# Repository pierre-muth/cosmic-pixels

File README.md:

# cosmic-pixels
Code and files of the cosmic-pixels project on www.pierremuth.com

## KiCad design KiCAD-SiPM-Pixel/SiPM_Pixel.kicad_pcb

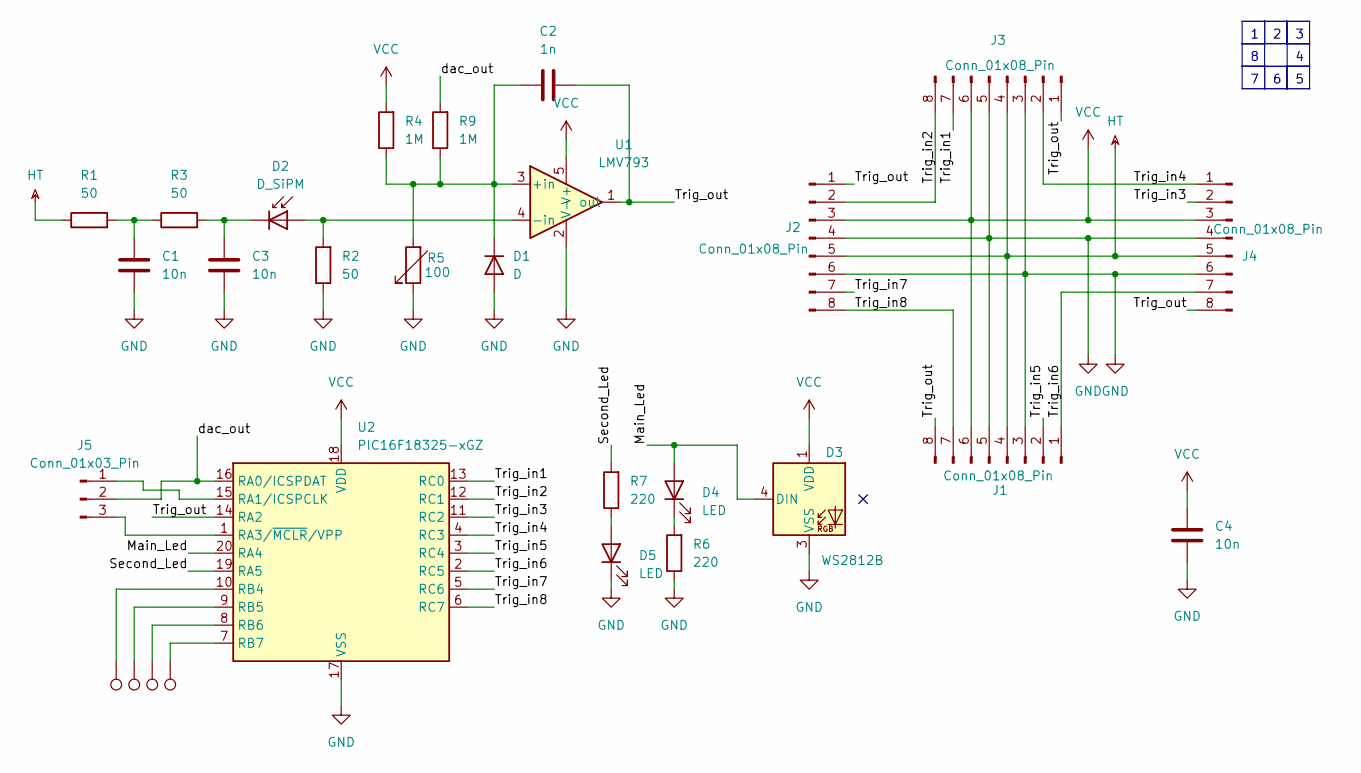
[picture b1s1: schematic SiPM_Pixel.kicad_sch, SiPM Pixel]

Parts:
C1, C3, C4: 10n; C_0805_2012Metric_Pad1.18x1.45mm_HandSolder
C2: 1n; C_0805_2012Metric_Pad1.18x1.45mm_HandSolder
D1: D; D_0805_2012_long_HandSolder
D2: D_SiPM; PinSocket_1x02_P2.54mm_Vertical
D3: WS2812B; LED_WS2812B_5.0x5.0mm_3Pin
D4, D5: LED; LED_0805_2012Metric_Pad1.15x1.40mm_HandSolder
J1, J2, J3, J4: Conn_01x08_Pin; PinHeader_1x08_P2.54mm_Vertical
J5: Conn_01x03_Pin; PinHeader_1x03_P2.54mm_Vertical_small_ring
R1, R2, R3: 50; R_0805_2012Metric_Pad1.20x1.40mm_HandSolder
R4, R9: 1M; R_0805_2012Metric_Pad1.20x1.40mm_HandSolder
R5: 100; R_0805_and_5x5Pot_HandSolder
R6, R7: 220; R_0805_2012Metric_Pad1.20x1.40mm_HandSolder
U1: LMV793; SOT-23-5_HandSoldering
U2: PIC16F18325-xGZ; UQFN-20-1EP_4x4mm_P0.5mm_easy_solder
b4, b5, b6, b7: TestPoint; TestPoint_Pad_1x1mm

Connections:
/Main_Led: D3.4 (DIN), D4.2 (A), U2.20 (RA4)
/Second_Led: R7.2, U2.19 (RA5)
/Trig_in1: J3.7, U2.13 (RC0)
/Trig_in2: J2.2, J3.8, U2.12 (RC1)
/Trig_in3: J4.2, U2.11 (RC2)
/Trig_in4: J3.2, J4.1, U2.4 (RC3)
/Trig_in5: J1.2, U2.3 (RC4)
/Trig_in6: J1.1, J4.7, U2.2 (RC5)
/Trig_in7: J2.7, U2.5 (RC6)
/Trig_in8: J1.7, J2.8, U2.6 (RC7)
/Trig_out: C2.1, J1.8, J2.1, J3.1, J4.8, U1.1 (out), U2.14 (RA2)
/dac_out: J5.2, R9.2, U2.16 (RA0/ICSPDAT)
GND: C1.2, C3.2, C4.2, D1.2 (A), D3.3 (VSS), D5.1 (K), J1.3, J1.5, J2.4, J2.6, J3.3, J3.5, J4.4, J4.6, R2.1, R5.1, R6.1, U1.2 (V-), U2.17 (VSS), U2.21 (VSS)
HT: J1.4, J2.5, J3.4, J4.5, R1.1
unnamed: C1.1, R1.2, R3.1
unnamed: C2.2, D1.1 (K), R4.1, R5.2, R9.1, U1.3 (+in)
unnamed: D2.2 (A), R2.2, U1.4 (-in)
unnamed: C3.1, D2.1 (K), R3.2
unnamed: D4.1 (K), R6.2
unnamed: D5.2 (A), R7.1
unnamed: J5.1, U2.15 (RA1/ICSPCLK)
unnamed: J5.3, U2.1 (RA3/~MCLR/VPP)
unnamed: U2.10 (RB4), b4.1
unnamed: U2.9 (RB5), b5.1
unnamed: U2.8 (RB6), b6.1
unnamed: U2.7 (RB7), b7.1
VCC: C4.1, D3.1 (VDD), J1.6, J2.3, J3.6, J4.3, R4.2, U1.5 (V+), U2.18 (VDD)

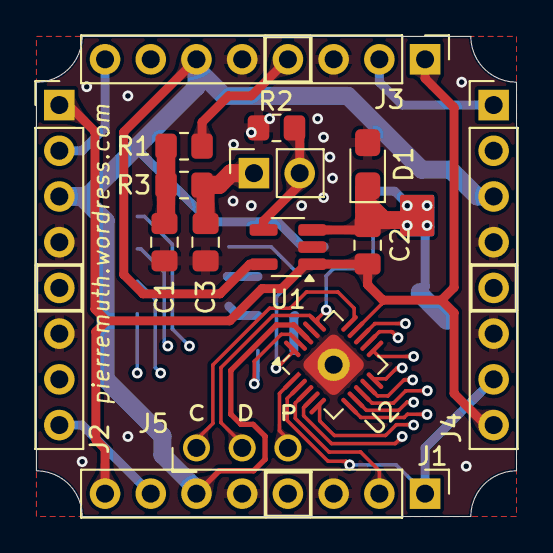
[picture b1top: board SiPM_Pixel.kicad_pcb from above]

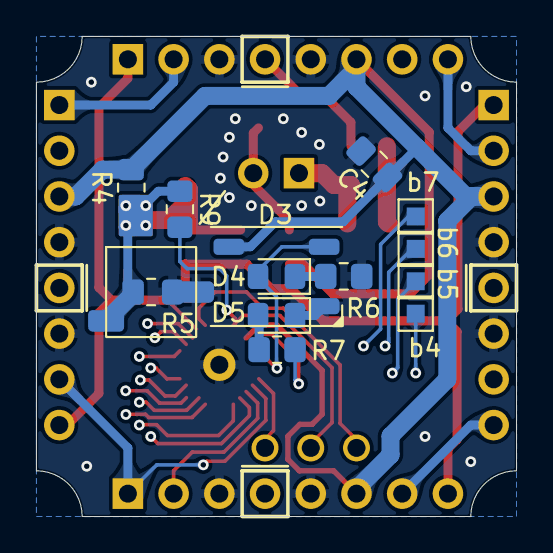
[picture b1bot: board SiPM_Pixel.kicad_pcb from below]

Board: 4 copper layers, 26.7 x 26.7 mm, 28 parts (13 on the bottom side), 27 nets.

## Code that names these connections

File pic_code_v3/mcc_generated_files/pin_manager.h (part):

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#define RA0_SetHigh()            do { LATAbits.LATA0 = 1; } while(0)
#define RA0_SetLow()             do { LATAbits.LATA0 = 0; } while(0)
#define RA0_Toggle()             do { LATAbits.LATA0 = ~LATAbits.LATA0; } while(0)
#define RA0_GetValue()              PORTAbits.RA0
#define RA0_SetDigitalInput()    do { TRISAbits.TRISA0 = 1; } while(0)
#define RA0_SetDigitalOutput()   do { TRISAbits.TRISA0 = 0; } while(0)
#define RA0_SetPullup()             do { WPUAbits.WPUA0 = 1; } while(0)
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#define RA1_SetHigh()            do { LATAbits.LATA1 = 1; } while(0)
#define RA1_SetLow()             do { LATAbits.LATA1 = 0; } while(0)
#define RA1_Toggle()             do { LATAbits.LATA1 = ~LATAbits.LATA1; } while(0)
#define RA1_GetValue()              PORTAbits.RA1
#define RA1_SetDigitalInput()    do { TRISAbits.TRISA1 = 1; } while(0)
#define RA1_SetDigitalOutput()   do { TRISAbits.TRISA1 = 0; } while(0)
#define RA1_SetPullup()             do { WPUAbits.WPUA1 = 1; } while(0)
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#define RA2_SetHigh()            do { LATAbits.LATA2 = 1; } while(0)
#define RA2_SetLow()             do { LATAbits.LATA2 = 0; } while(0)
#define RA2_Toggle()             do { LATAbits.LATA2 = ~LATAbits.LATA2; } while(0)
#define RA2_GetValue()              PORTAbits.RA2
#define RA2_SetDigitalInput()    do { TRISAbits.TRISA2 = 1; } while(0)
#define RA2_SetDigitalOutput()   do { TRISAbits.TRISA2 = 0; } while(0)
#define RA2_SetPullup()             do { WPUAbits.WPUA2 = 1; } while(0)
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// get/set Main_Led aliases
#define Main_Led_TRIS                 TRISAbits.TRISA4
#define Main_Led_LAT                  LATAbits.LATA4
#define Main_Led_PORT                 PORTAbits.RA4
#define Main_Led_WPU                  WPUAbits.WPUA4
#define Main_Led_OD                   ODCONAbits.ODCA4
#define Main_Led_ANS                  ANSELAbits.ANSA4
#define Main_Led_SetHigh()            do { LATAbits.LATA4 = 1; } while(0)
#define Main_Led_SetLow()             do { LATAbits.LATA4 = 0; } while(0)
#define Main_Led_Toggle()             do { LATAbits.LATA4 = ~LATAbits.LATA4; } while(0)
#define Main_Led_GetValue()           PORTAbits.RA4
#define Main_Led_SetDigitalInput()    do { TRISAbits.TRISA4 = 1; } while(0)
#define Main_Led_SetDigitalOutput()   do { TRISAbits.TRISA4 = 0; } while(0)
#define Main_Led_SetPullup()          do { WPUAbits.WPUA4 = 1; } while(0)
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// get/set Second_Led aliases
#define Second_Led_TRIS                 TRISAbits.TRISA5
#define Second_Led_LAT                  LATAbits.LATA5
#define Second_Led_PORT                 PORTAbits.RA5
#define Second_Led_WPU                  WPUAbits.WPUA5
#define Second_Led_OD                   ODCONAbits.ODCA5
#define Second_Led_ANS                  ANSELAbits.ANSA5
#define Second_Led_SetHigh()            do { LATAbits.LATA5 = 1; } while(0)
#define Second_Led_SetLow()             do { LATAbits.LATA5 = 0; } while(0)
#define Second_Led_Toggle()             do { LATAbits.LATA5 = ~LATAbits.LATA5; } while(0)
#define Second_Led_GetValue()           PORTAbits.RA5
#define Second_Led_SetDigitalInput()    do { TRISAbits.TRISA5 = 1; } while(0)
#define Second_Led_SetDigitalOutput()   do { TRISAbits.TRISA5 = 0; } while(0)
#define Second_Led_SetPullup()          do { WPUAbits.WPUA5 = 1; } while(0)
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#define RB4_SetHigh()            do { LATBbits.LATB4 = 1; } while(0)
#define RB4_SetLow()             do { LATBbits.LATB4 = 0; } while(0)
#define RB4_Toggle()             do { LATBbits.LATB4 = ~LATBbits.LATB4; } while(0)
#define RB4_GetValue()              PORTBbits.RB4
#define RB4_SetDigitalInput()    do { TRISBbits.TRISB4 = 1; } while(0)
#define RB4_SetDigitalOutput()   do { TRISBbits.TRISB4 = 0; } while(0)
#define RB4_SetPullup()             do { WPUBbits.WPUB4 = 1; } while(0)
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#define RB5_SetHigh()            do { LATBbits.LATB5 = 1; } while(0)
#define RB5_SetLow()             do { LATBbits.LATB5 = 0; } while(0)
#define RB5_Toggle()             do { LATBbits.LATB5 = ~LATBbits.LATB5; } while(0)
#define RB5_GetValue()              PORTBbits.RB5
#define RB5_SetDigitalInput()    do { TRISBbits.TRISB5 = 1; } while(0)
#define RB5_SetDigitalOutput()   do { TRISBbits.TRISB5 = 0; } while(0)
#define RB5_SetPullup()             do { WPUBbits.WPUB5 = 1; } while(0)
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// get/set Sync_out aliases
#define Sync_out_TRIS                 TRISBbits.TRISB6
#define Sync_out_LAT                  LATBbits.LATB6
#define Sync_out_PORT                 PORTBbits.RB6
#define Sync_out_WPU                  WPUBbits.WPUB6
#define Sync_out_OD                   ODCONBbits.ODCB6
#define Sync_out_ANS                  ANSELBbits.ANSB6
#define Sync_out_SetHigh()            do { LATBbits.LATB6 = 1; } while(0)
#define Sync_out_SetLow()             do { LATBbits.LATB6 = 0; } while(0)
#define Sync_out_Toggle()             do { LATBbits.LATB6 = ~LATBbits.LATB6; } while(0)
#define Sync_out_GetValue()           PORTBbits.RB6
#define Sync_out_SetDigitalInput()    do { TRISBbits.TRISB6 = 1; } while(0)
#define Sync_out_SetDigitalOutput()   do { TRISBbits.TRISB6 = 0; } while(0)
#define Sync_out_SetPullup()          do { WPUBbits.WPUB6 = 1; } while(0)
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// get/set Sync_in aliases
#define Sync_in_TRIS                 TRISBbits.TRISB7
#define Sync_in_LAT                  LATBbits.LATB7
#define Sync_in_PORT                 PORTBbits.RB7
#define Sync_in_WPU                  WPUBbits.WPUB7
#define Sync_in_OD                   ODCONBbits.ODCB7
#define Sync_in_ANS                  ANSELBbits.ANSB7
#define Sync_in_SetHigh()            do { LATBbits.LATB7 = 1; } while(0)
#define Sync_in_SetLow()             do { LATBbits.LATB7 = 0; } while(0)
#define Sync_in_Toggle()             do { LATBbits.LATB7 = ~LATBbits.LATB7; } while(0)
#define Sync_in_GetValue()           PORTBbits.RB7
#define Sync_in_SetDigitalInput()    do { TRISBbits.TRISB7 = 1; } while(0)
#define Sync_in_SetDigitalOutput()   do { TRISBbits.TRISB7 = 0; } while(0)
#define Sync_in_SetPullup()          do { WPUBbits.WPUB7 = 1; } while(0)
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// get/set Trig_in1 aliases
#define Trig_in1_TRIS                 TRISCbits.TRISC0
#define Trig_in1_LAT                  LATCbits.LATC0
#define Trig_in1_PORT                 PORTCbits.RC0
#define Trig_in1_WPU                  WPUCbits.WPUC0
#define Trig_in1_OD                   ODCONCbits.ODCC0
#define Trig_in1_ANS                  ANSELCbits.ANSC0
#define Trig_in1_SetHigh()            do { LATCbits.LATC0 = 1; } while(0)
#define Trig_in1_SetLow()             do { LATCbits.LATC0 = 0; } while(0)
#define Trig_in1_Toggle()             do { LATCbits.LATC0 = ~LATCbits.LATC0; } while(0)
#define Trig_in1_GetValue()           PORTCbits.RC0
#define Trig_in1_SetDigitalInput()    do { TRISCbits.TRISC0 = 1; } while(0)
#define Trig_in1_SetDigitalOutput()   do { TRISCbits.TRISC0 = 0; } while(0)
#define Trig_in1_SetPullup()          do { WPUCbits.WPUC0 = 1; } while(0)
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// get/set Trig_in2 aliases
#define Trig_in2_TRIS                 TRISCbits.TRISC1
#define Trig_in2_LAT                  LATCbits.LATC1
#define Trig_in2_PORT                 PORTCbits.RC1
#define Trig_in2_WPU                  WPUCbits.WPUC1
#define Trig_in2_OD                   ODCONCbits.ODCC1
#define Trig_in2_ANS                  ANSELCbits.ANSC1
#define Trig_in2_SetHigh()            do { LATCbits.LATC1 = 1; } while(0)
#define Trig_in2_SetLow()             do { LATCbits.LATC1 = 0; } while(0)
#define Trig_in2_Toggle()             do { LATCbits.LATC1 = ~LATCbits.LATC1; } while(0)
#define Trig_in2_GetValue()           PORTCbits.RC1
#define Trig_in2_SetDigitalInput()    do { TRISCbits.TRISC1 = 1; } while(0)
#define Trig_in2_SetDigitalOutput()   do { TRISCbits.TRISC1 = 0; } while(0)
#define Trig_in2_SetPullup()          do { WPUCbits.WPUC1 = 1; } while(0)
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// get/set Trig_in3 aliases
#define Trig_in3_TRIS                 TRISCbits.TRISC2
#define Trig_in3_LAT                  LATCbits.LATC2
#define Trig_in3_PORT                 PORTCbits.RC2
#define Trig_in3_WPU                  WPUCbits.WPUC2
#define Trig_in3_OD                   ODCONCbits.ODCC2
#define Trig_in3_ANS                  ANSELCbits.ANSC2
#define Trig_in3_SetHigh()            do { LATCbits.LATC2 = 1; } while(0)
#define Trig_in3_SetLow()             do { LATCbits.LATC2 = 0; } while(0)
#define Trig_in3_Toggle()             do { LATCbits.LATC2 = ~LATCbits.LATC2; } while(0)
#define Trig_in3_GetValue()           PORTCbits.RC2
#define Trig_in3_SetDigitalInput()    do { TRISCbits.TRISC2 = 1; } while(0)
#define Trig_in3_SetDigitalOutput()   do { TRISCbits.TRISC2 = 0; } while(0)
#define Trig_in3_SetPullup()          do { WPUCbits.WPUC2 = 1; } while(0)
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// get/set Trig_in4 aliases
#define Trig_in4_TRIS                 TRISCbits.TRISC3
#define Trig_in4_LAT                  LATCbits.LATC3
#define Trig_in4_PORT                 PORTCbits.RC3
#define Trig_in4_WPU                  WPUCbits.WPUC3
#define Trig_in4_OD                   ODCONCbits.ODCC3
#define Trig_in4_ANS                  ANSELCbits.ANSC3
#define Trig_in4_SetHigh()            do { LATCbits.LATC3 = 1; } while(0)
#define Trig_in4_SetLow()             do { LATCbits.LATC3 = 0; } while(0)
#define Trig_in4_Toggle()             do { LATCbits.LATC3 = ~LATCbits.LATC3; } while(0)
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

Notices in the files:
pic_code_v3/mcc_generated_files/pin_manager.h:
(c) 2018 Microchip Technology Inc. and its subsidiaries.
